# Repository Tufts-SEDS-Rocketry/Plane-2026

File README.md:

# SEDSna
### A plane by Tufts Rocketry

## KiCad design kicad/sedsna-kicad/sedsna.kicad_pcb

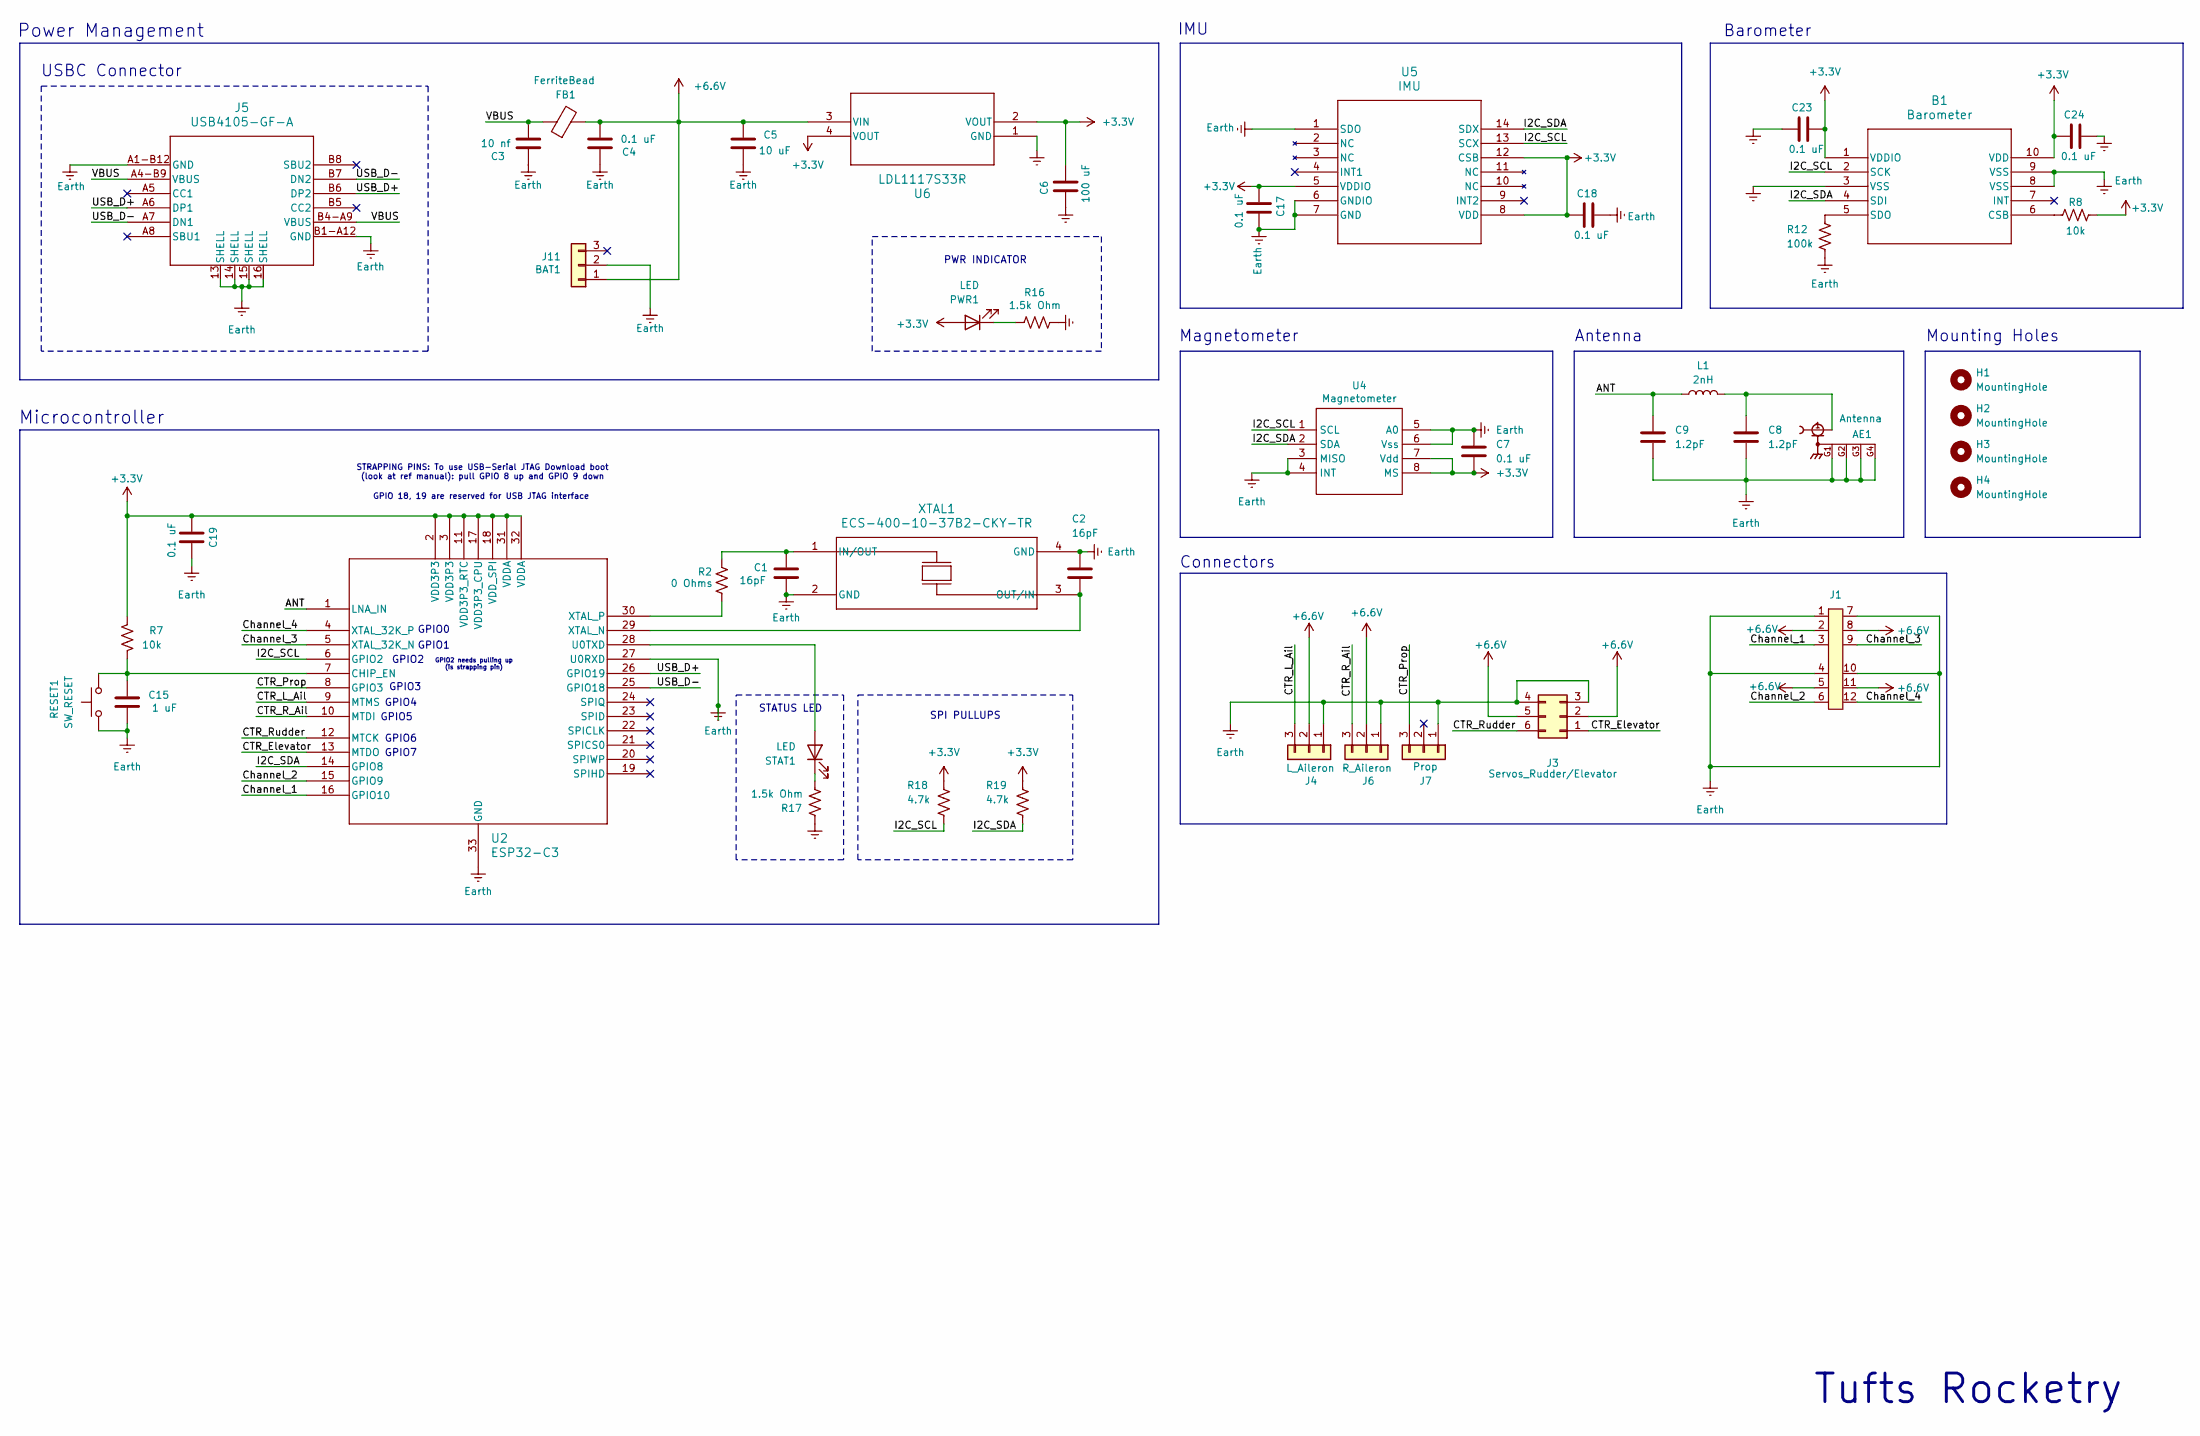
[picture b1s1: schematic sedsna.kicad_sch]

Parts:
AE1: Antenna; GRADCONN_RFPC-SMA28-F; PARTREV 1.0
B1: Barometer; QFN10_BMP581_BOS
C1, C2: 16pF; C_0402_1005Metric_Pad0.74x0.62mm_HandSolder
C3: 10 nf; C_0603_1608Metric
C4, C7, C17, C18, C19, C23, C24: 0.1 uF; CAP_CL05_SAM
C5: 10 uF; C_0805_2012Metric
C6: 100 uF; C_1206_3216Metric
C8, C9: 1.2pF; C_0201_0603Metric_Pad0.64x0.40mm_HandSolder
C15: 1 uF; C_0603_1608Metric
FB1: FerriteBead; FB_MI0805K400R-10
H1, H2, H3, H4: MountingHole; mounting_hole
J1: Conn_04x03
J3: Servos_Rudder/Elevator; CONN06_2035551016_MOL
J4: L_Aileron; SHDR3W166P0X635_1X3_2032X762X1397P
J5: USB4105-GF-A; USB4105_GCT
J6: R_Aileron; SHDR3W166P0X635_1X3_2032X762X1397P
J7: Prop; SHDR3W166P0X635_1X3_2032X762X1397P
J11: BAT1; SHDR3W166P0X635_1X3_2032X762X1397P
L1: 2nH; L_0402_1005Metric_Pad0.77x0.64mm_HandSolder
PWR1: LED; 150080RS75000_WRE
R2: 0 Ohms; R_0603_1608Metric_Pad0.98x0.95mm_HandSolder
R7, R8: 10k; R_0603_1608Metric_Pad0.98x0.95mm_HandSolder
R12: 100k; R_0603_1608Metric_Pad0.98x0.95mm_HandSolder
R16, R17: 1.5k Ohm; R_0603_1608Metric_Pad0.98x0.95mm_HandSolder
R18, R19: 4.7k; R_0603_1608Metric_Pad0.98x0.95mm_HandSolder
RESET1: SW_RESET; 2-pronged_THT_button
STAT1: LED; 150080RS75000_WRE
U2: ESP32-C3; QFN32_5X5_EXP
U4: Magnetometer; MAGNETO-MLX90395KDC
U5: IMU; BMI323_BOS
U6: LDL1117S33R; SOT223_STM
XTAL1: ECS-400-10-37B2-CKY-TR; XTAL_ECS-400-10-37B2-CKY-TR

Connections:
+3.3V: B1.1 (VDDIO), B1.10 (VDD), C6.2, C7.2, C17.1, C18.1, C19.1, C23.2, C24.1, PWR1.2 (A), R7.1, R8.2, R18.1, R19.1, U2.2 (VDD3P3), U2.3 (VDD3P3), U2.11 (VDD3P3_RTC), U2.17 (VDD3P3_CPU), U2.18 (VDD_SPI), U2.31 (VDDA), U2.32 (VDDA), U4.7 (Vdd), U4.8 (MS), U5.5 (VDDIO), U5.8 (VDD), U5.12 (CSB), U6.2 (VOUT), U6.4 (VOUT)
+6.6V: C4.1, C5.2, FB1.2, J1.2, J1.5, J1.8, J1.11, J3.2, J3.5, J4.2, J6.2, J11.1, U6.3 (VIN)
/ANT: C9.1, L1.1, U2.1 (LNA_IN)
/CTR_Elevator: J3.1, U2.13 (MTDO)
/CTR_L_Ail: J4.3, U2.9 (MTMS)
/CTR_Prop: J7.3, U2.8 (GPIO3)
/CTR_R_Ail: J6.3, U2.10 (MTDI)
/CTR_Rudder: J3.6, U2.12 (MTCK)
/Channel_1: J1.3, U2.16 (GPIO10)
/Channel_2: J1.6, U2.15 (GPIO9)
/Channel_3: J1.9, U2.5 (XTAL_32K_N)
/Channel_4: J1.12, U2.4 (XTAL_32K_P)
/I2C_SCL: B1.2 (SCK), R18.2, U2.6 (GPIO2), U4.1 (SCL), U5.13 (SCX)
/I2C_SDA: B1.4 (SDI), R19.2, U2.14 (GPIO8), U4.2 (SDA), U5.14 (SDX)
/USB_D+: J5.A6 (DP1), J5.B6 (DP2), U2.26 (GPIO19)
/USB_D-: J5.A7 (DN1), J5.B7 (DN2), U2.25 (GPIO18)
/VBUS: C3.1, FB1.1, J5.A4-B9 (VBUS), J5.B4-A9 (VBUS)
Earth: AE1.G1, AE1.G2, AE1.G3, AE1.G4, B1.3 (VSS), B1.8 (VSS), B1.9 (VSS), C1.2, C2.1, C3.2, C4.2, C5.1, C6.1, C7.1, C8.2, C9.2, C15.1, C17.2, C18.2, C19.2, C23.1, C24.2, J1.1, J1.4, J1.7, J1.10, J3.3, J3.4, J4.1, J5.13 (SHELL), J5.14 (SHELL), J5.15 (SHELL), J5.16 (SHELL), J5.A1-B12 (GND), J5.B1-A12 (GND), J6.1, J7.1, J11.2, R12.2, R16.2, R17.2, RESET1.1, U2.27 (U0RXD), U2.33 (GND), U4.3 (MISO), U4.4 (INT), U4.5 (A0), U4.6 (Vss), U5.1 (SDO), U5.6 (GNDIO), U5.7 (GND), U6.1 (GND), XTAL1.2 (GND), XTAL1.4 (GND)
unnamed: AE1.1, C8.1, L1.2
unnamed: B1.6 (CSB), R8.1
unnamed: B1.5 (SDO), R12.1
unnamed: PWR1.1 (K), R16.1
unnamed: STAT1.2 (A), U2.28 (U0TXD)
unnamed: R17.1, STAT1.1 (K)
unnamed: C15.2, R7.2, RESET1.2, U2.7 (CHIP_EN)
unnamed: C2.2, U2.29 (XTAL_N), XTAL1.3 (OUT/IN)
unnamed: R2.1, U2.30 (XTAL_P)
unnamed: C1.1, R2.2, XTAL1.1 (IN/OUT)

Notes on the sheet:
GPIO2
STRAPPING PINS: To use USB-Serial JTAG Download boot (look at ref manual): pull GPIO 8 up and GPIO 9 down
GPIO6
Connectors
GPIO7
Microcontroller
GPIO4
GPIO 18, 19 are reserved for USB JTAG interface
SPI PULLUPS
Tufts Rocketry
USBC Connector
GPIO1
Barometer
STATUS LED
Mounting Holes
IMU
PWR INDICATOR
Power Management
Antenna
GPIO0
GPIO3
GPIO2 needs pulling up (is strapping pin)
GPIO5
Magnetometer

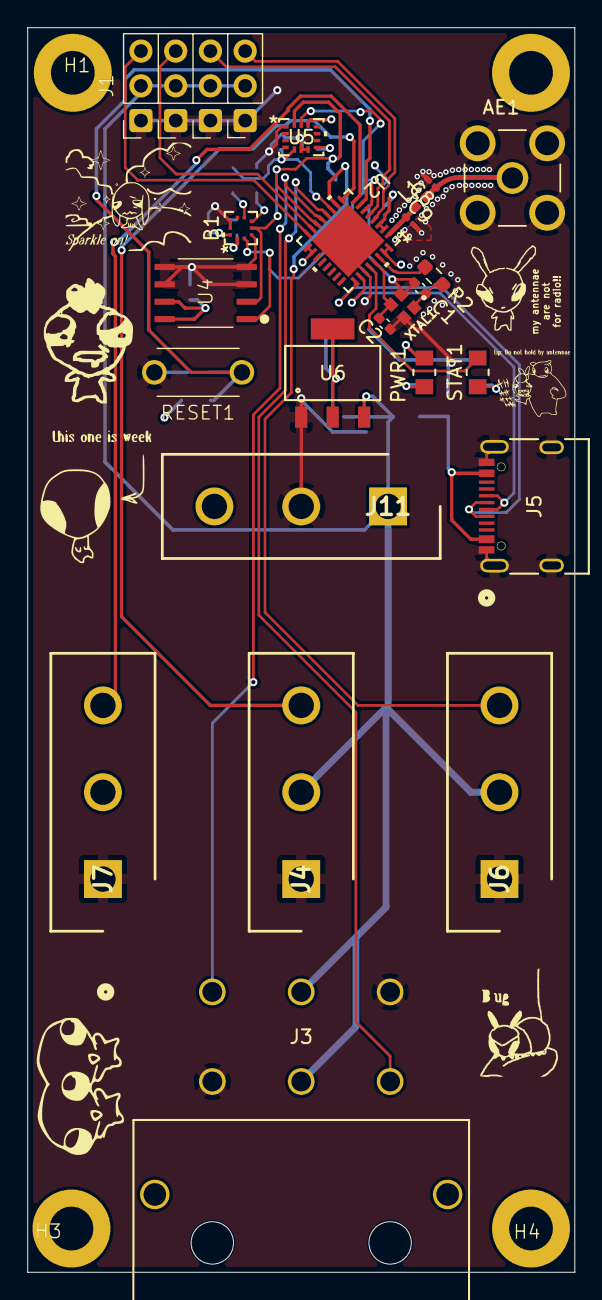
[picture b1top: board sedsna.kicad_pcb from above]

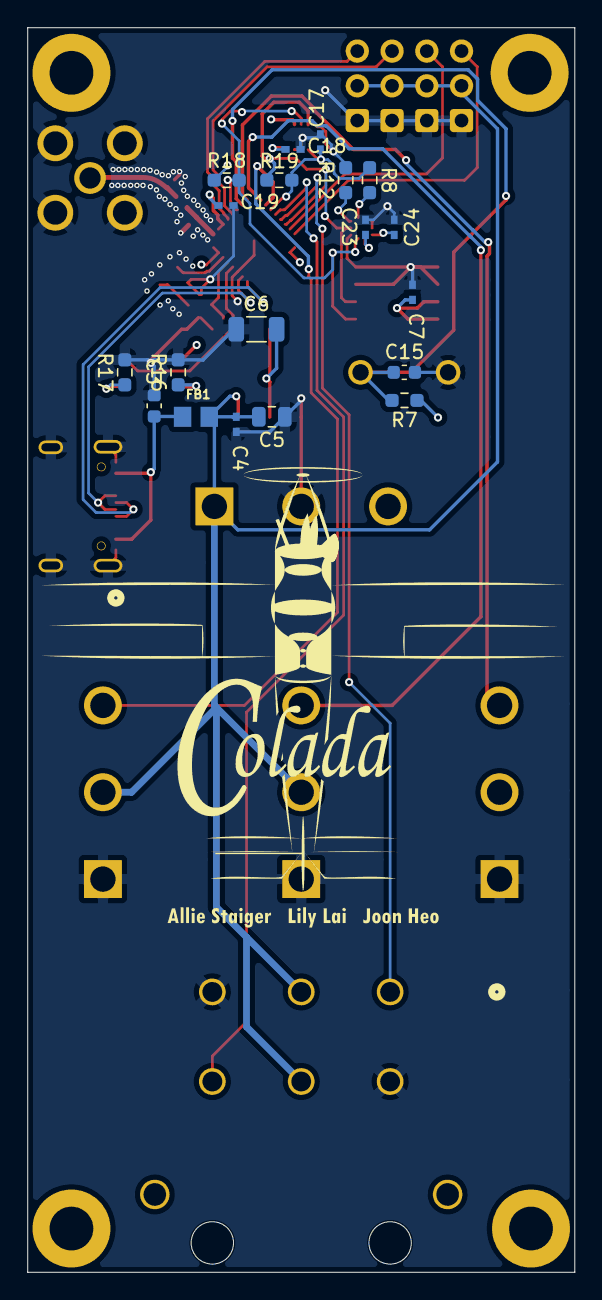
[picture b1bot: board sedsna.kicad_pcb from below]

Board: 4 copper layers, 40.0 x 91.0 mm, 46 parts (19 on the bottom side), 28 nets.
